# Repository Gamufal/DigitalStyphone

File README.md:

# Digital Stylophone

A microcontroller-based stylophone with recording and playback capabilities, built around the Raspberry Pi Pico. This project reimagines the classic analog instrument with modern digital features, including an OLED display and non-volatile memory for storing recorded tracks.

## Demo

## Features

*   **Sound Generation:** Produces a square wave tone with a classic synthesizer sound.
*   **Multiple Octaves:** Three selectable octaves (low, middle, high).
*   **Volume Control:** Adjustable volume with 8 levels.
*   **Recording & Playback:** Record, save, and play back musical sequences.
*   **Persistent Memory:** Saves the recorded track and user settings (volume, octave) to a `settings.json` file on the device.
*   **OLED Display Interface:** A 128x64 SSD1306 OLED screen provides a menu-based interface for all functions.
*   **Tactile Controls:** 5-button navigation for intuitive menu control.
*   **Portable Design:** Powered by a 9V battery for on-the-go use.
*   **Raspberry Pi Pico Core:** Utilizes a Raspberry Pi Pico for all processing and hardware control.

## Hardware

### Components

| Component | Quantity |
|---|---|
| Raspberry Pi Pico | 1 |
| 5mm LED | 2 |
| 10Ω Resistor (1/4W) | 1 |
| 1kΩ Resistor (1/4W) | 21 |
| 10kΩ Resistor (1/4W) | 1 |
| 10uF Capacitor | 1 |
| 0.96" OLED Display | 1 |
| LM2596 Step-down Converter | 1 |
| 6x6mm Tactile Switch | 5 |
| Female Pin Headers | 5 |
| Latching Switch | 1 |
| 9V Battery | 1 |
| 1W 8Ohm Speaker | 1 |

### Schematic

### PCB Design

### Manufacture Preview

### 3D Housing Model

A 3D-printed enclosure can also be made for the device. A model of the enclosure has been prepared for this purpose, and it is available as the `housing.stl` file.

## Software

### How it Works

The device is controlled by a MicroPython script (`main.py`) running on the Raspberry Pi Pico.

*   **Sound Generation:** The stylus's position on the resistive keyboard is read as an analog value by the Pico's ADC (Analog-to-Digital Converter). This value is then mapped to a specific musical note frequency. The sound is generated using PWM (Pulse Width Modulation) sent to a 1W speaker.

*   **UI & Menu:** A menu-driven interface is displayed on the 128x64 OLED screen. The user navigates the menu using a 5-button keypad. The available options are Volume, Tone (Octave), Record, and Play.

*   **Recording & Playback:** The recording function captures a sequence of notes and their timings. It records pairs of `(frequency, timestamp)` to a list. The playback function iterates through the recorded list, playing back the notes with the correct timing.

*   **Persistence:** The recorded song, as well as the volume and tone settings, are saved to a `settings.json` file in the Pico's flash memory. This allows the device to retain settings and recordings between power cycles.

### Installation

1.  **Install MicroPython:** If you haven't already, install MicroPython on your Raspberry Pi Pico. You can find the official instructions [here](https://www.raspberrypi.com/documentation/microcontrollers/micropython.html).

2.  **Install `ssd1306.py`:** The OLED display requires the `ssd1306.py` library. You can find it [here](https://github.com/micropython/micropython/blob/master/drivers/display/ssd1306.py) and save it to your Pico.

3.  **Upload the Software:** Copy the `main.py` file to your Raspberry Pi Pico. The easiest way to do this is by using an IDE like [Thonny](https://thonny.org/), which has a simple interface for managing files on a MicroPython device.

## User Guide

### Controls

| Control | Function |
|---|---|
| Up/Down Buttons | Navigate through the main menu. |
| Left/Right Buttons | Decrease/increase the volume or tone (octave). |
| OK Button | Select a menu option; start/stop recording or playback. |
| Stylus | Play notes by touching the corresponding keys. |

### Operation

1.  **Power On:** Connect a 9V battery and flip the power switch. The green LED will light up, and the main menu will appear on the OLED display.
2.  **Play Music:** Simply touch the stylus to any of the metal keys to play a note.
3.  **Navigate Menu:** Use the **Up** and **Down** buttons to highlight a menu option.
4.  **Select Option:** Press the **OK** button to enter the selected menu (Volume, Tone, Record, or Play).
5.  **Adjust Volume/Tone:** In the Volume or Tone menus, use the **Left** and **Right** buttons to make adjustments. Press **Up** or **Down** to exit and save.
6.  **Record:** Select "RECORD" from the main menu and press **OK**. Press **OK** again to start recording. The red LED will blink. Play your tune, and press **OK** to stop. The recording will be saved automatically.
7.  **Playback:** Select "PLAY" from the main menu and press **OK**. Press **OK** again to start playback of the last recorded track. The red LED will stay lit during playback.

## Troubleshooting

| Symptom | Possible Cause | Suggested Solution |
|---|---|---|
| Screen works, but the green power LED is off. | The green LED is burnt out. | Replace the green LED. |
| The green power LED is on, but the screen is blank. | The OLED display is damaged or disconnected. | Check the display's connections. If the problem persists, replace the display module. |
| Nothing works (no screen, no LEDs). | The 9V battery is dead. | Replace the 9V battery. |
| The screen and LEDs work, but there is no sound. | The speaker is damaged or disconnected. | Check the speaker wiring. If the problem persists, replace the speaker. |

## Future Improvements

*   **Enhanced Sound Engine:**
    *   Add a vibrato effect using a Low-Frequency Oscillator (LFO).
*   **Connectivity:**
    *   Add MIDI output via USB, allowing the stylophone to function as a MIDI controller.
*   **Code Refinements:**
    *   Refactor the code for better efficiency, especially the recording and display update logic.

## License

This project is licensed under the MIT License. See the `LICENSE` file for details.

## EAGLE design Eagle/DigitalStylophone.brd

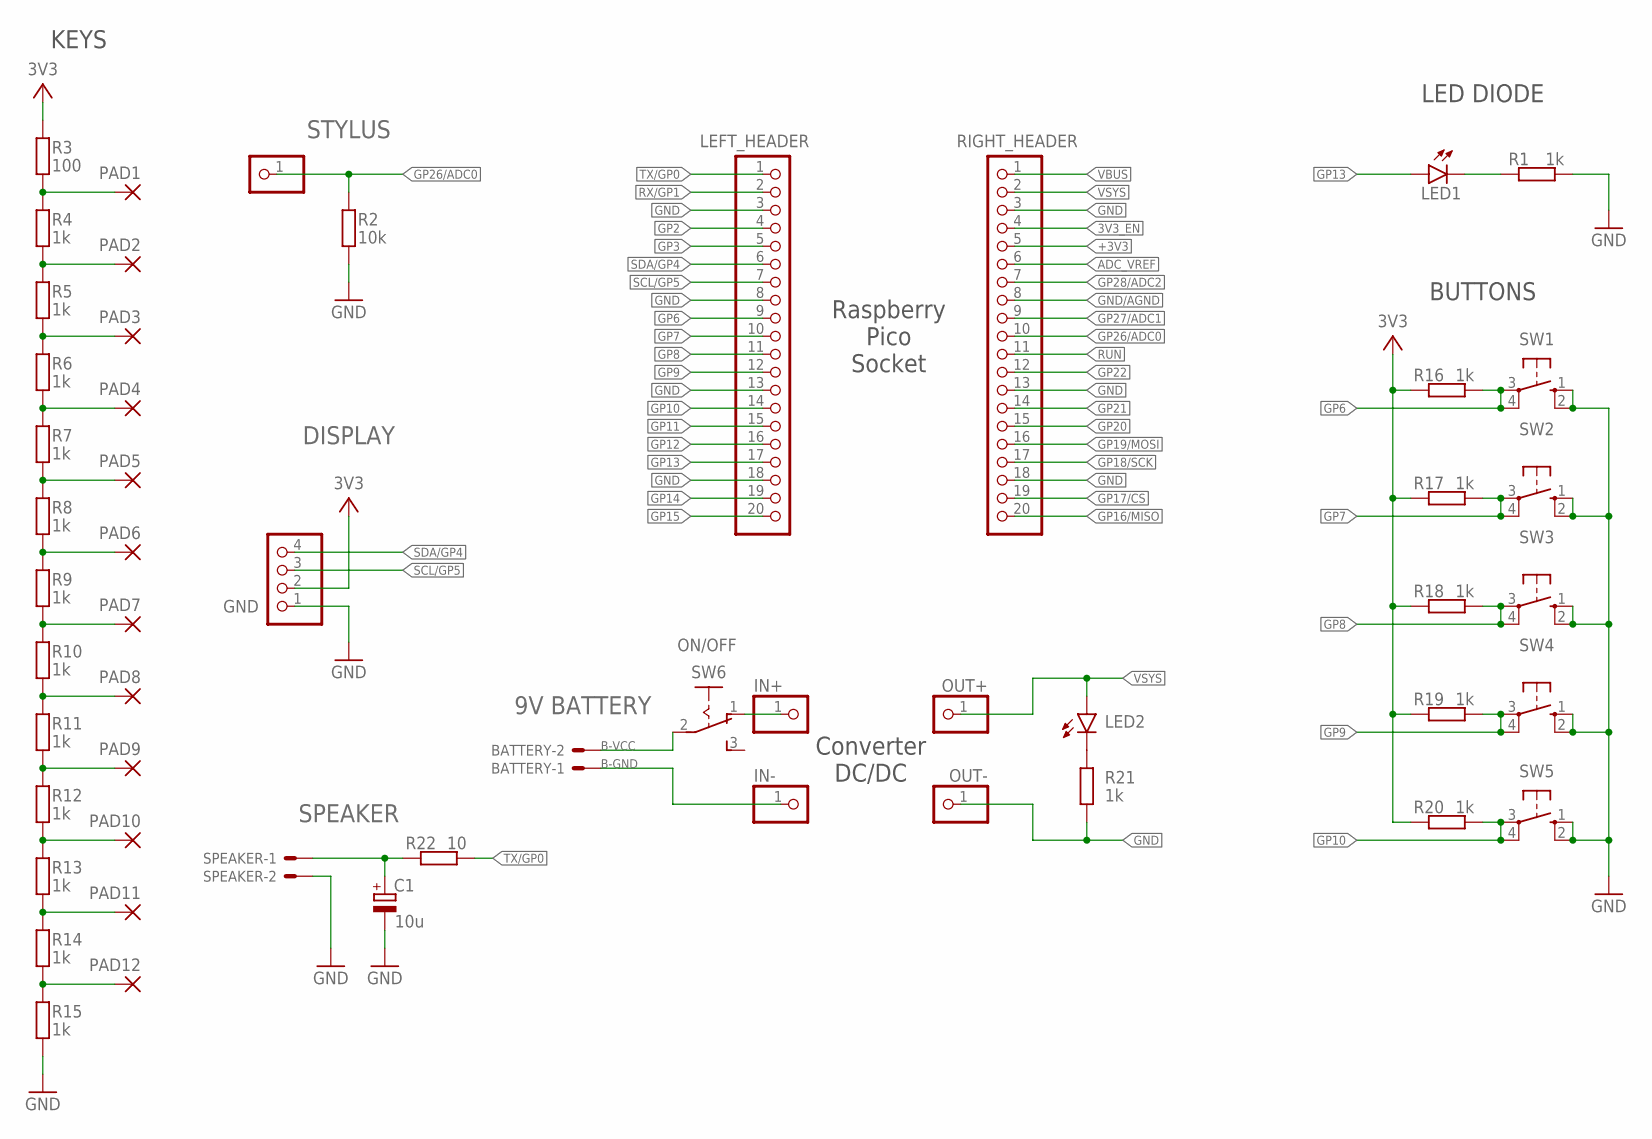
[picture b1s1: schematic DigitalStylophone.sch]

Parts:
BATTERY: 9V BATTERY; 22-23-2021
C1: 10u; E2,5-5
DISPLAY: GND; 1X04
IN+: PINHD-1X1; 1X01
IN-: PINHD-1X1; 1X01
LED1: LED5MM
LED2: LED3MM
LEFT_HEADER: PINHD-1X20; 1X20
OUT+: PINHD-1X1; 1X01
OUT-: PINHD-1X1; 1X01
PAD1, PAD2, PAD3, PAD4, PAD5, PAD6, PAD7, PAD8, PAD9, PAD10, PAD11, PAD12: SMD5; SMD2,54-5,08
R1, R4, R5, R6, R7, R8, R9, R10, R11, R12, R13, R14, R15, R16, R17, R18, R19, R20, R21: 1k; 0204/7
R2: 10k; 0204/7
R3: 100; 0204/7
R22: 10; 0204/7
RIGHT_HEADER: PINHD-1X20; 1X20
SPEAKER: SPEAKER; 22-23-2021
STYLUS: PINHD-1X1; 1X01
SW1, SW2, SW3, SW4, SW5: 10-XX; B3F-10XX
SW6: ON/OFF; 255SB

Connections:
3V3_EN: RIGHT_HEADER.4
+3V3: DISPLAY.2, R3.2, R16.2, R17.2, R18.2, R19.2, R20.2, RIGHT_HEADER.5
ADC_VREF: RIGHT_HEADER.6
B-GND: BATTERY.1, IN-.1
B-SW: IN+.1, SW6.1 (O)
B-VCC: BATTERY.2, SW6.2
GND: C1.-, DISPLAY.1, LEFT_HEADER.3, LEFT_HEADER.8, LEFT_HEADER.13, LEFT_HEADER.18, OUT-.1, R1.1, R2.1, R15.1, R21.1, RIGHT_HEADER.3, RIGHT_HEADER.13, RIGHT_HEADER.18, SPEAKER.2, SW1.1 (S), SW1.2 (S1), SW2.1 (S), SW2.2 (S1), SW3.1 (S), SW3.2 (S1), SW4.1 (S), SW4.2 (S1), SW5.1 (S), SW5.2 (S1)
GND/AGND: RIGHT_HEADER.8
GP2: LEFT_HEADER.4
GP3: LEFT_HEADER.5
GP6: LEFT_HEADER.9, R16.1, SW1.3, SW1.4 (P1)
GP7: LEFT_HEADER.10, R17.1, SW2.3, SW2.4 (P1)
GP8: LEFT_HEADER.11, R18.1, SW3.3, SW3.4 (P1)
GP9: LEFT_HEADER.12, R19.1, SW4.3, SW4.4 (P1)
GP10: LEFT_HEADER.14, R20.1, SW5.3, SW5.4 (P1)
GP11: LEFT_HEADER.15
GP12: LEFT_HEADER.16
GP13: LED1.A, LEFT_HEADER.17
GP14: LEFT_HEADER.19
GP15: LEFT_HEADER.20
GP16/MISO: RIGHT_HEADER.20
GP17/CS: RIGHT_HEADER.19
GP18/SCK: RIGHT_HEADER.17
GP19/MOSI: RIGHT_HEADER.16
GP20: RIGHT_HEADER.15
GP21: RIGHT_HEADER.14
GP22: RIGHT_HEADER.12
GP26/ADC0: R2.2, RIGHT_HEADER.10, STYLUS.1
GP27/ADC1: RIGHT_HEADER.9
GP28/ADC2: RIGHT_HEADER.7
LED: LED1.K (C), R1.2
unnamed: C1.+, R22.2, SPEAKER.1
unnamed: LED2.K (C), R21.2
P1: PAD1.1, R3.1, R4.2
P2: PAD2.1, R4.1, R5.2
P3: PAD3.1, R5.1, R6.2
P4: PAD4.1, R6.1, R7.2
P5: PAD5.1, R7.1, R8.2
P6: PAD6.1, R8.1, R9.2
P7: PAD7.1, R9.1, R10.2
P8: PAD8.1, R10.1, R11.2
P9: PAD9.1, R11.1, R12.2
P10: PAD10.1, R12.1, R13.2
P11: PAD11.1, R13.1, R14.2
P12: PAD12.1, R14.1, R15.2
RUN: RIGHT_HEADER.11
RX/GP1: LEFT_HEADER.2
SCL/GP5: DISPLAY.3, LEFT_HEADER.7
SDA/GP4: DISPLAY.4, LEFT_HEADER.6
TX/GP0: LEFT_HEADER.1, R22.1
VBUS: RIGHT_HEADER.1
VSYS: LED2.A, OUT+.1, RIGHT_HEADER.2

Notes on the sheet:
Raspberry Pico Socket
KEYS
LED DIODE
BUTTONS
Converter DC/DC

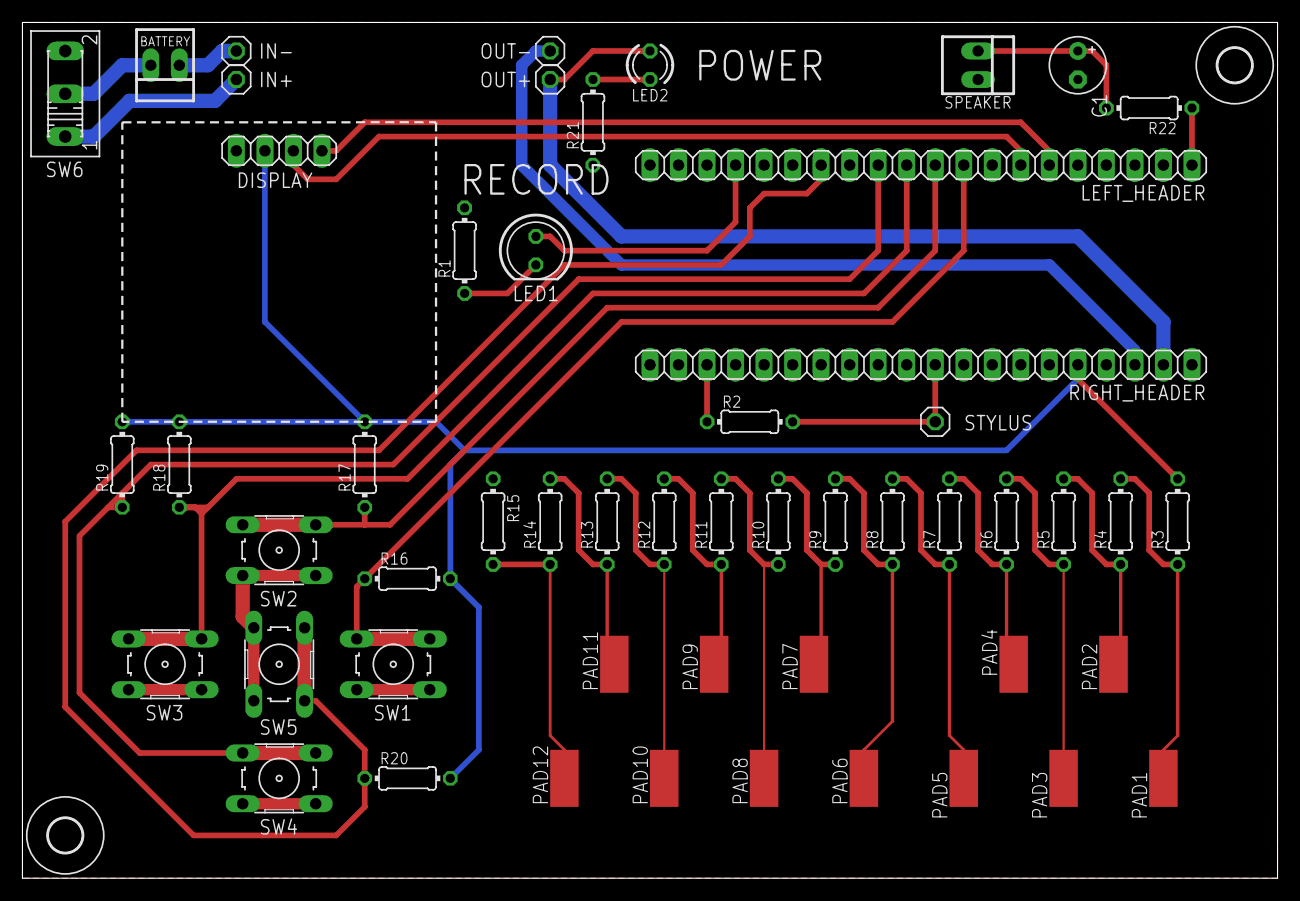
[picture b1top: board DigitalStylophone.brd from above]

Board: 2 copper layers, 111.8 x 76.2 mm, 55 parts (0 on the bottom side), 31 nets.

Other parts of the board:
U$1, U$2: 3,0

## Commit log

2025-09-29 Updated LICENSE
2025-09-29 Added eagle files
2025-09-29 Added images
2025-09-29 Added pico software
2025-09-29 Added image of a prototype
2025-09-29 adding stylophone case
2025-09-29 added stl preview
2025-09-29 Bigger size
